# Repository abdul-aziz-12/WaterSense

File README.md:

# WaterSense
->A project of Water Motor Automation System
-> Contrains Arduino and Eagle PCB files for whole working project

Note: It also contains previous versions files.

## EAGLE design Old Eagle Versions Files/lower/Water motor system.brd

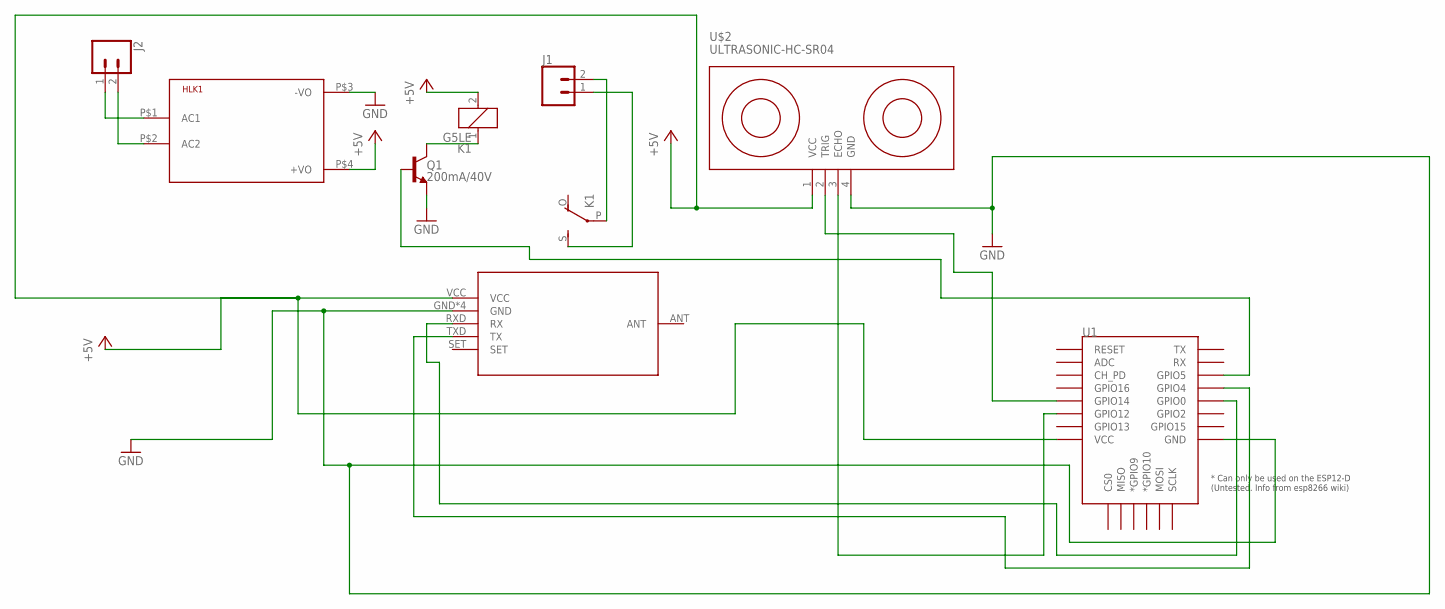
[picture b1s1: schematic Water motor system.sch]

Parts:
HLK1: HLK-PM013W; HLK-PM01
J1, J2: CONN_025MM; SCREWTERMINAL-5MM-2
K1: G5LE
Q1: 200mA/40V; TO-92
U1: ESP12ESMD; ESP12E-SMD
U$2: ULTRASONIC-HC-SR04
U$3: HC-12_FOOTPRINT

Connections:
+5V: HLK1.P$4 (+VO), K1.2, U1.VCC, U$2.1 (VCC), U$3.VCC
GND: HLK1.P$3 (-VO), Q1.1 (E), U1.GND, U$2.4 (GND), U$3.GND, U$3.GND1 (GND), U$3.GND2 (GND), U$3.MCHFIX (GND)
unnamed: U1.GPIO4, U$3.TXD (TX)
unnamed: U1.GPIO12, U$2.3 (ECHO)
unnamed: Q1.2 (B), U1.GPIO5
unnamed: J1.1, K1.S
unnamed: J1.2, K1.P
unnamed: K1.1, Q1.3 (C)
unnamed: HLK1.P$2 (AC2), J2.2
unnamed: HLK1.P$1 (AC1), J2.1
unnamed: U1.GPIO0, U$3.RXD (RX)
unnamed: U1.GPIO14, U$2.2 (TRIG)

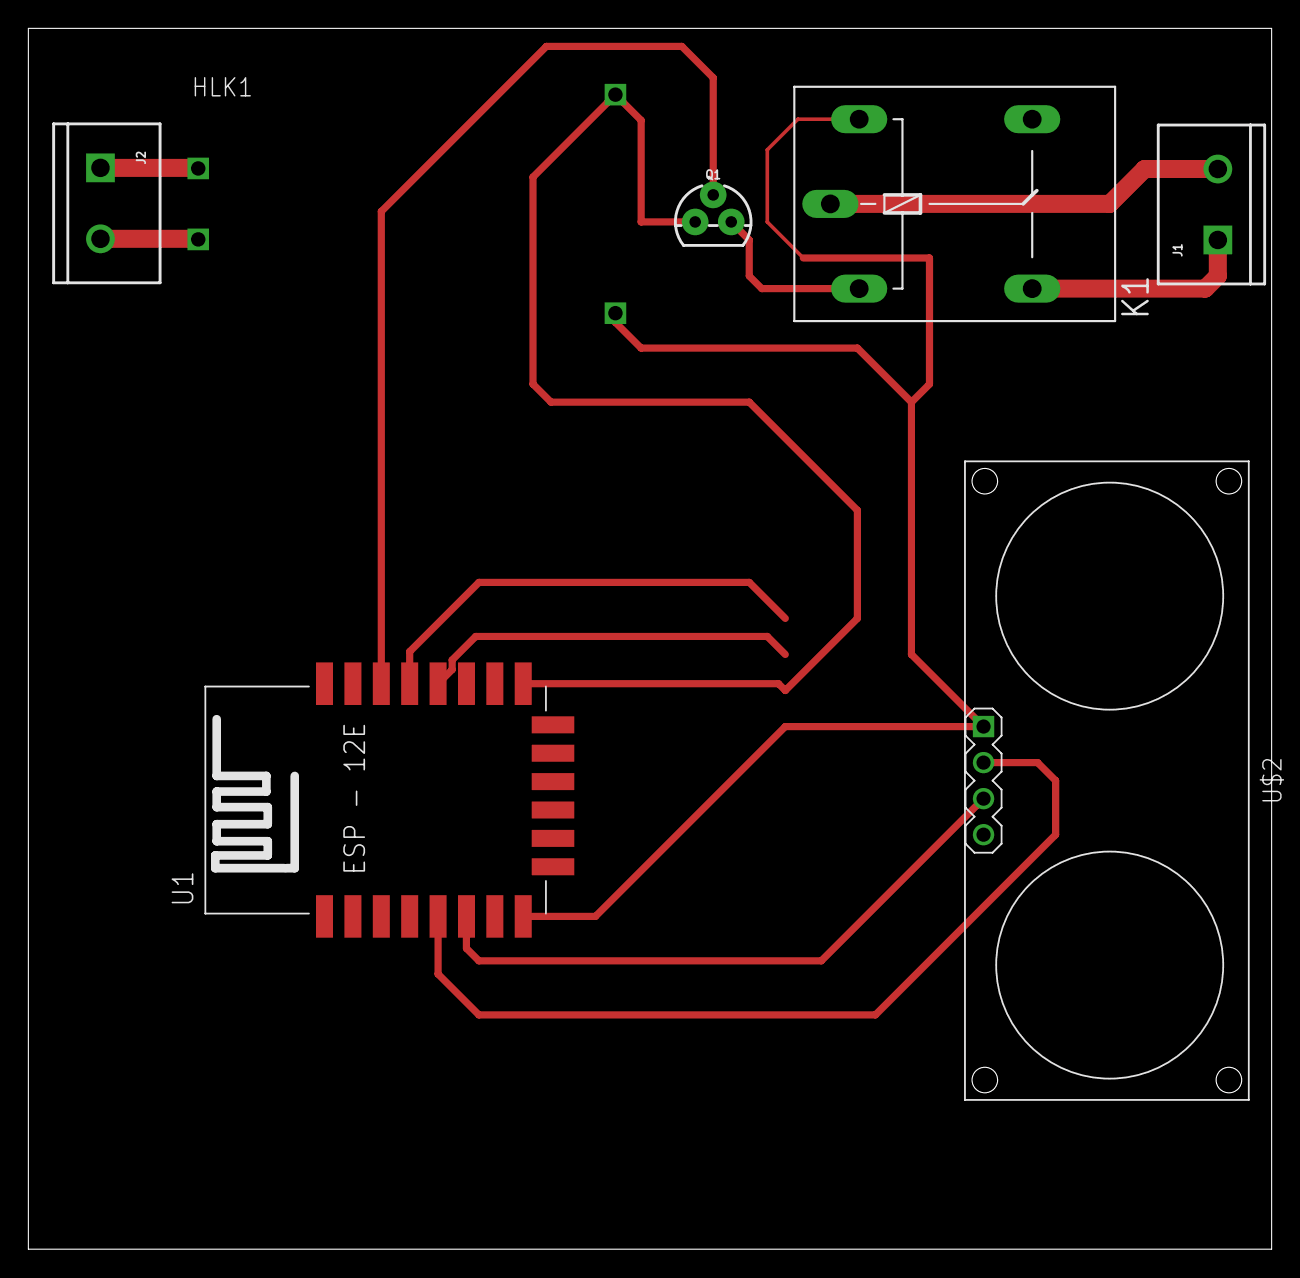
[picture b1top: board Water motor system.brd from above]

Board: 2 copper layers, 87.6 x 86.0 mm, 8 parts (1 on the bottom side), 12 nets.

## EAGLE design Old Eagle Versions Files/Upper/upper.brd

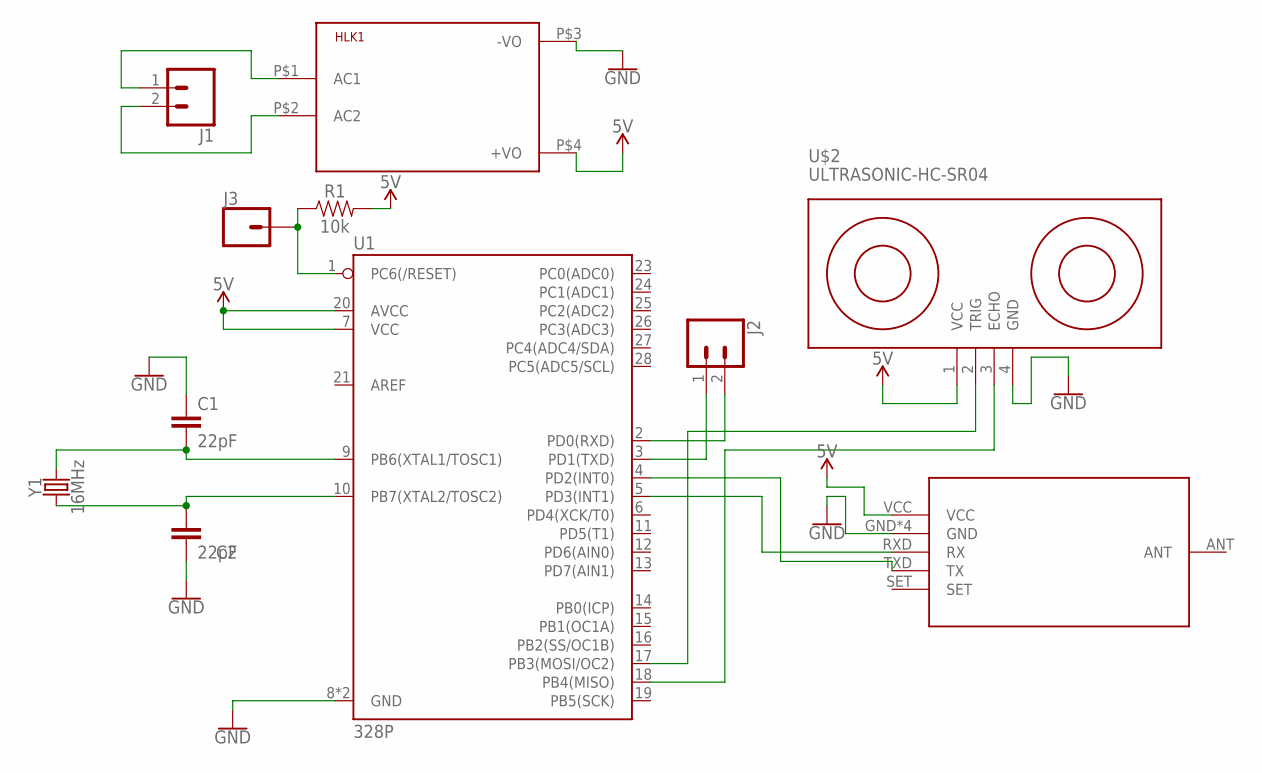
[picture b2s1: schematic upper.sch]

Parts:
C1, C2: 22pF; CAP-PTH-2.54
HLK1: HLK-PM013W; HLK-PM01
J1, J2: CONN_025MM; SCREWTERMINAL-5MM-2
J3: CONN_01; 1X01
R1: 10k; AXIAL-0.3
U1: 328P; DIP28
U$1: HC-12_FOOTPRINT
U$2: ULTRASONIC-HC-SR04
Y1: 16MHz; HC49US

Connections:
5V: HLK1.P$4 (+VO), R1.P$2 (2), U1.7 (VCC), U1.20 (AVCC), U$1.VCC, U$2.1 (VCC)
GND: C1.1, C2.2, HLK1.P$3 (-VO), U1.8 (GND), U1.22 (GND), U$1.GND, U$1.GND1 (GND), U$1.GND2 (GND), U$1.MCHFIX (GND), U$2.4 (GND)
unnamed: U1.4 (PD2(INT0)), U$1.TXD (TX)
unnamed: U1.17 (PB3(MOSI/OC2)), U$2.2 (TRIG)
unnamed: U1.18 (PB4(MISO)), U$2.3 (ECHO)
unnamed: U1.5 (PD3(INT1)), U$1.RXD (RX)
unnamed: HLK1.P$2 (AC2), J1.2
unnamed: HLK1.P$1 (AC1), J1.1
unnamed: J3.1, R1.P$1 (1), U1.1 (PC6(/RESET))
unnamed: J2.1, U1.3 (PD1(TXD))
unnamed: J2.2, U1.2 (PD0(RXD))
unnamed: C1.2, U1.9 (PB6(XTAL1/TOSC1)), Y1.2
unnamed: C2.1, U1.10 (PB7(XTAL2/TOSC2)), Y1.1

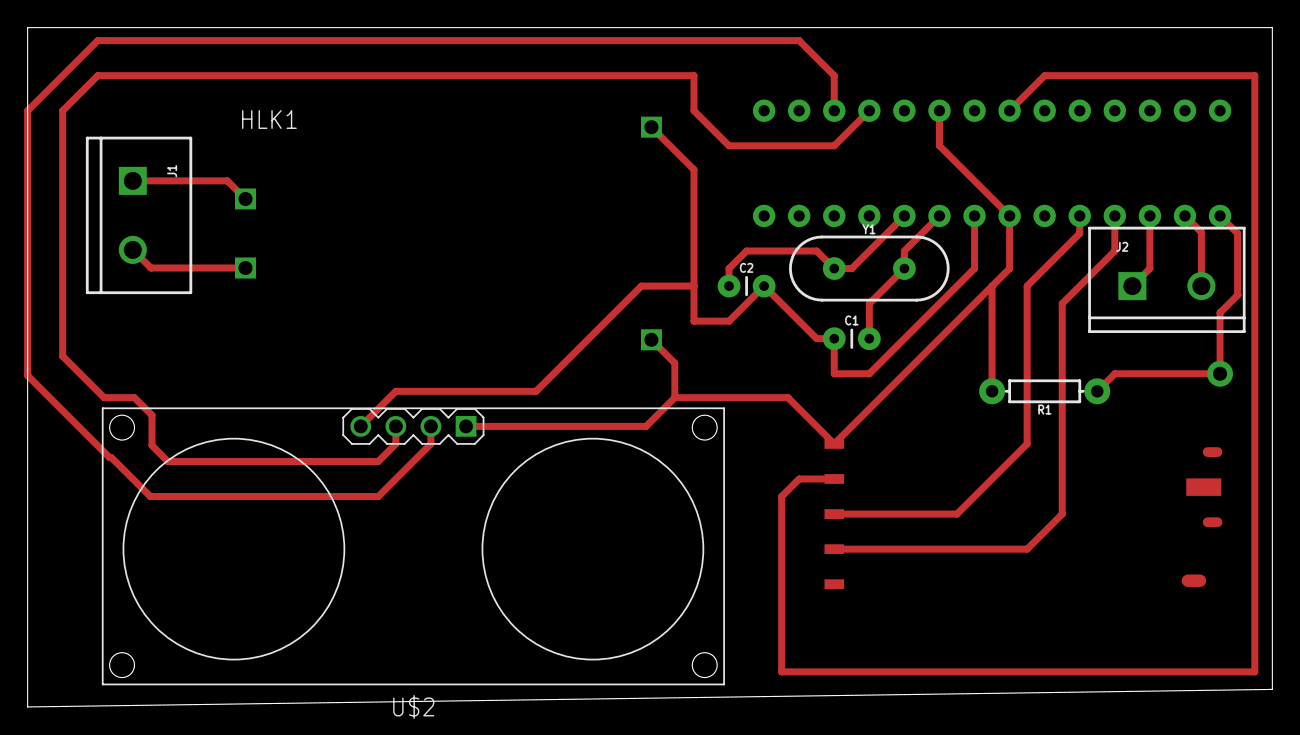
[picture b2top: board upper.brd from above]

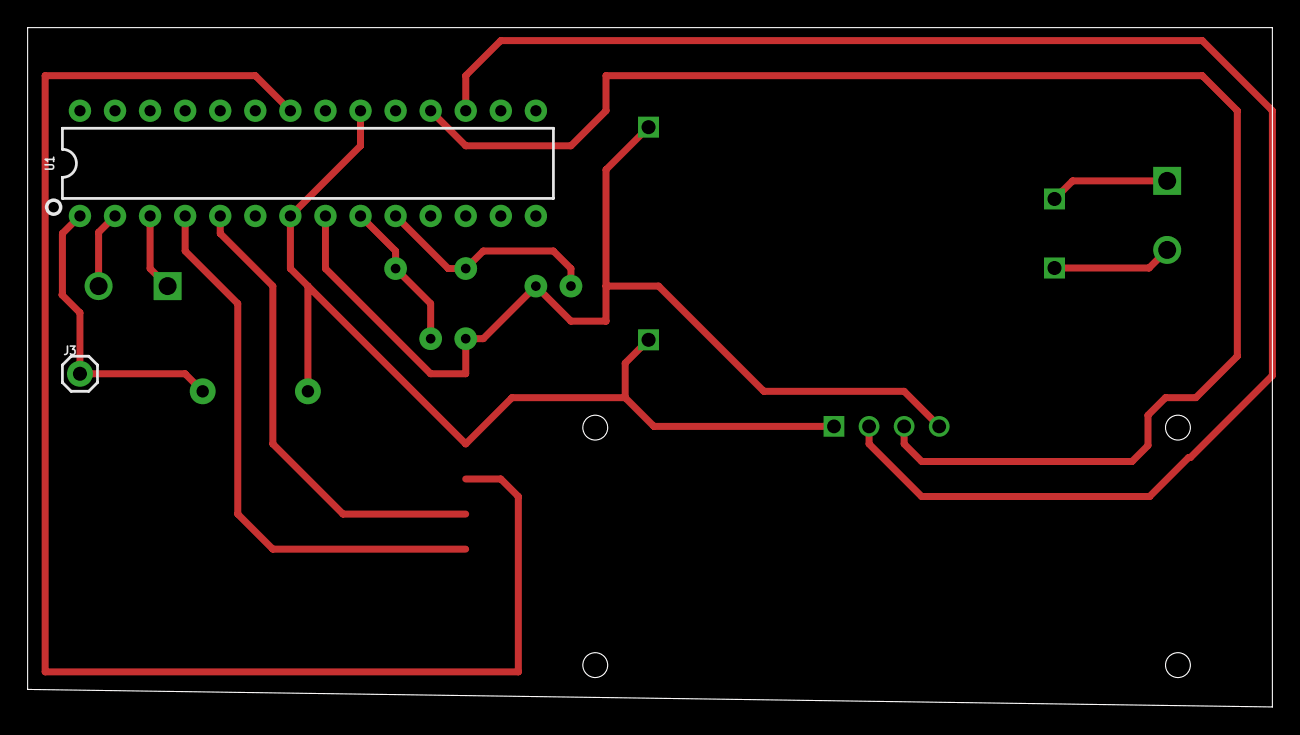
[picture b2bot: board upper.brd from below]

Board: 2 copper layers, 90.2 x 49.2 mm, 11 parts (2 on the bottom side), 13 nets.

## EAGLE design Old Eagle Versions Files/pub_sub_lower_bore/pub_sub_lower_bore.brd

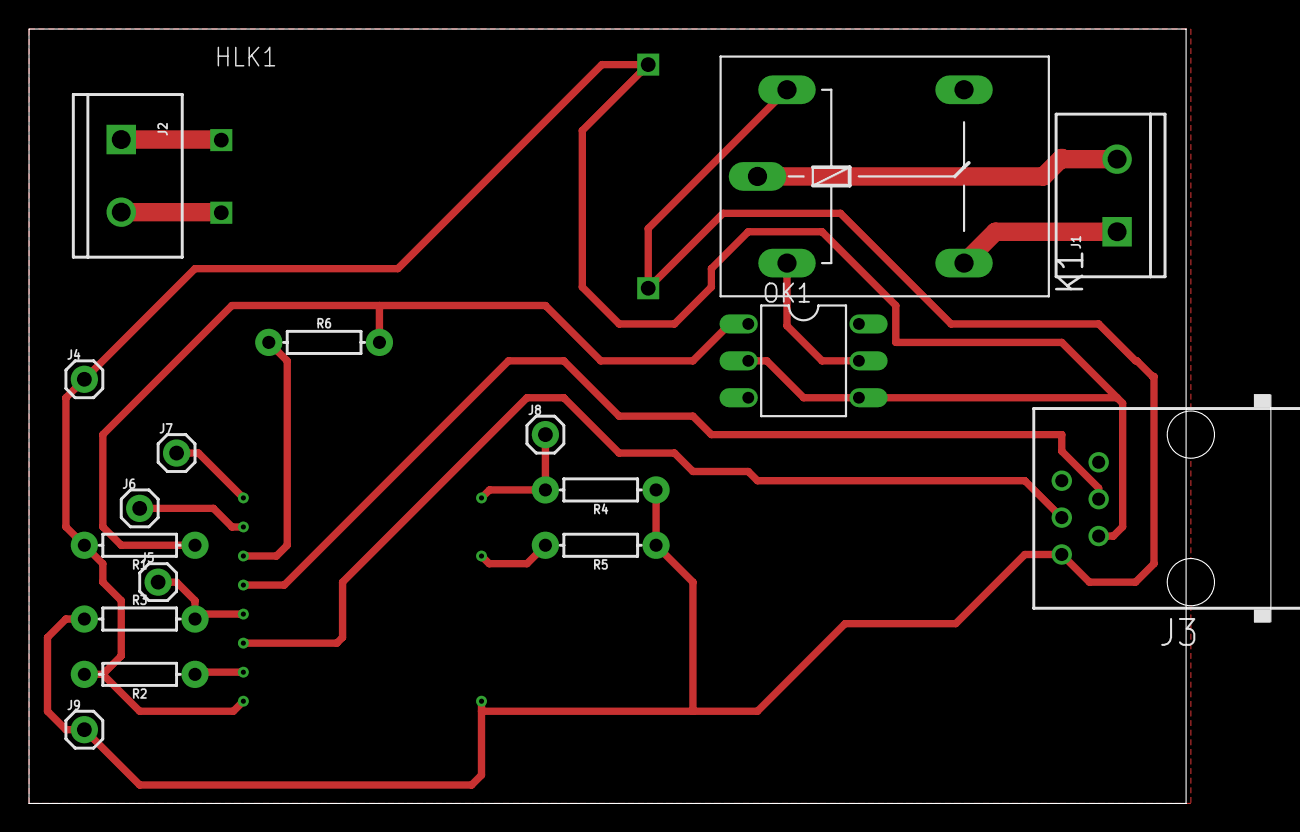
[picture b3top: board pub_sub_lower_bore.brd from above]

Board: 2 copper layers, 85.5 x 53.3 mm, 19 parts (1 on the bottom side), 17 nets.

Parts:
HLK1: HLK-PM013W; HLK-PM01
J1, J2: SCREWTERMINAL-5MM-2
J3: RJ11-6L-B; RJ11-NO_SHIELD
J4, J5, J6, J7, J8, J9: 1X01
K1: G5LE
OK1: 4N35; DIL06
R1: 10k; AXIAL-0.3
R2, R3, R4, R5, R6: 1k; AXIAL-0.3
U1: ESP12E-SMD

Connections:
+5V: HLK1.P$4, J3.1, J9.1, K1.2, R3.P$1, R4.P$1, R5.P$1, U1.VCC
GND: HLK1.P$3, J3.2, J4.1, OK1.2, OK1.4, R1.P$2, R2.P$2, U1.GND
unnamed: J3.4, U1.GPIO4
unnamed: OK1.1, R1.P$1, R6.P$2
unnamed: R2.P$1, U1.GPIO15
unnamed: J5.1, R3.P$2, U1.GPIO0
unnamed: R6.P$1, U1.GPIO5
unnamed: J1.1, K1.S
unnamed: J1.2, K1.P
unnamed: K1.1, OK1.5
unnamed: HLK1.P$2, J2.2
unnamed: HLK1.P$1, J2.1
unnamed: J3.3, U1.GPIO2
unnamed: J7.1, U1.TXD0
unnamed: J6.1, U1.RXD0
unnamed: J8.1, R4.P$2, U1.RESET
unnamed: R5.P$2, U1.CH_PD

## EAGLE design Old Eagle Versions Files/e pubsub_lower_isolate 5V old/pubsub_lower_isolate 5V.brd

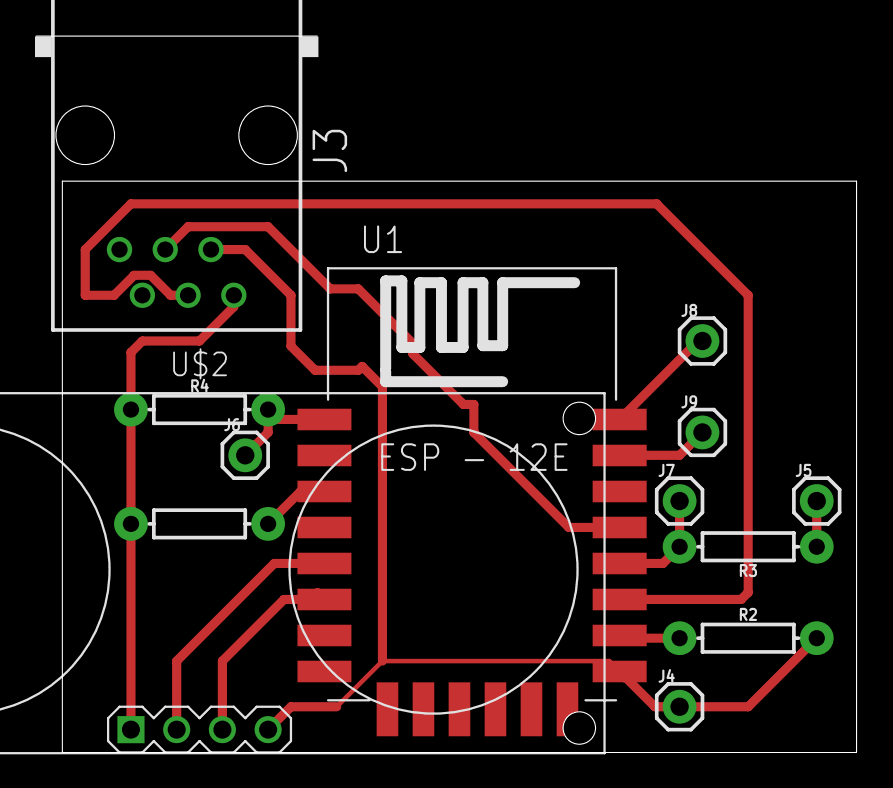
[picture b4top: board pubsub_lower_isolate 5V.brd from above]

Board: 2 copper layers, 44.1 x 31.7 mm, 13 parts (0 on the bottom side), 12 nets.

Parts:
J3: RJ11-6L-B; RJ11-NO_SHIELD
J4, J5, J6, J7, J8, J9: 1X01
R2, R3, R4, R5: 1k; AXIAL-0.3
U1: ESP12E-SMD
U$2: ULTRASONIC-HC-SR04

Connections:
+5V: J3.1, J5.1, R3.P$1, R4.P$1, R5.P$1, U1.VCC, U$2.1
GND: J3.2, J4.1, R2.P$2, U1.GND, U$2.4
unnamed: J3.4, U1.GPIO4
unnamed: R2.P$1, U1.GPIO15
unnamed: J7.1, R3.P$2, U1.GPIO0
unnamed: J9.1, U1.RXD0
unnamed: U1.GPIO12, U$2.3
unnamed: J3.3, U1.GPIO2
unnamed: U1.GPIO14, U$2.2
unnamed: J8.1, U1.TXD0
unnamed: J6.1, R4.P$2, U1.RESET
unnamed: R5.P$2, U1.CH_PD

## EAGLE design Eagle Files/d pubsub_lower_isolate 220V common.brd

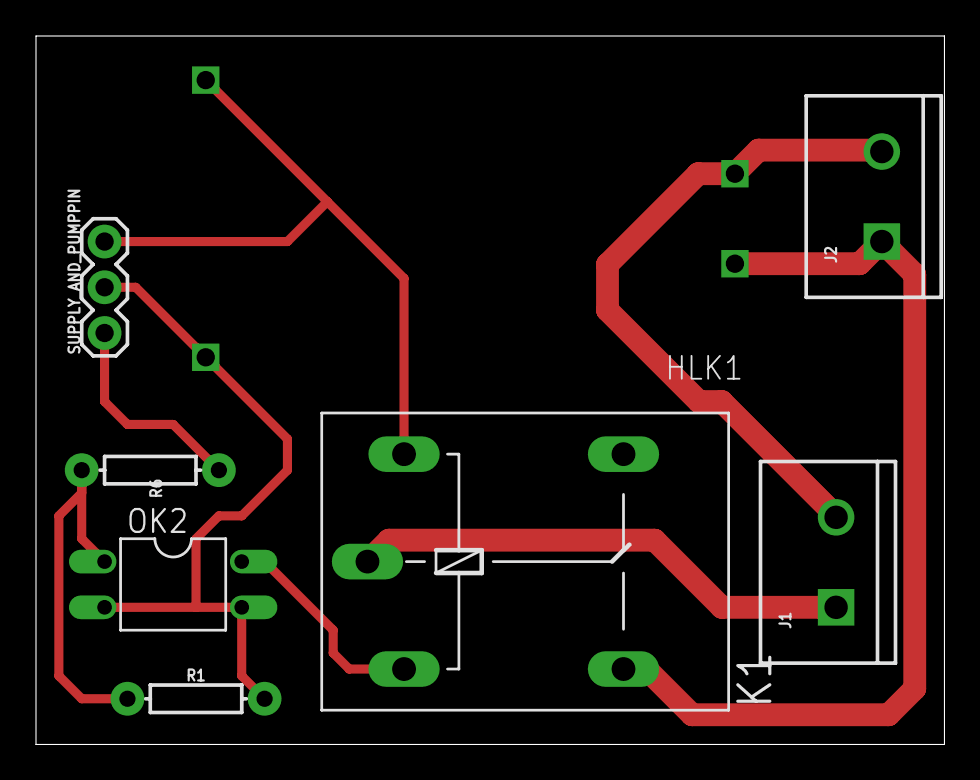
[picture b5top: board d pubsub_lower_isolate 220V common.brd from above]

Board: 2 copper layers, 50.5 x 39.4 mm, 8 parts (0 on the bottom side), 8 nets.

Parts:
HLK1: HLK-PM013W; HLK-PM01
J1, J2: SCREWTERMINAL-5MM-2
K1: G5LE
OK2: PC817; DIL04
R1: 10k; AXIAL-0.3
R6: 1k; AXIAL-0.3
SUPPLY_AND_PUMPPIN: 455-1750-1-ND; 1X03

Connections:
+5V: HLK1.P$4, K1.2, SUPPLY_AND_PUMPPIN.3
GND: HLK1.P$3, OK2.2, OK2.3, R1.P$2, SUPPLY_AND_PUMPPIN.2
unnamed: OK2.1, R1.P$1, R6.P$2
unnamed: HLK1.P$1, J2.1, K1.S
unnamed: J1.1, K1.P
unnamed: K1.1, OK2.4
unnamed: HLK1.P$2, J1.2, J2.2
PUMP_PIN: R6.P$1, SUPPLY_AND_PUMPPIN.1

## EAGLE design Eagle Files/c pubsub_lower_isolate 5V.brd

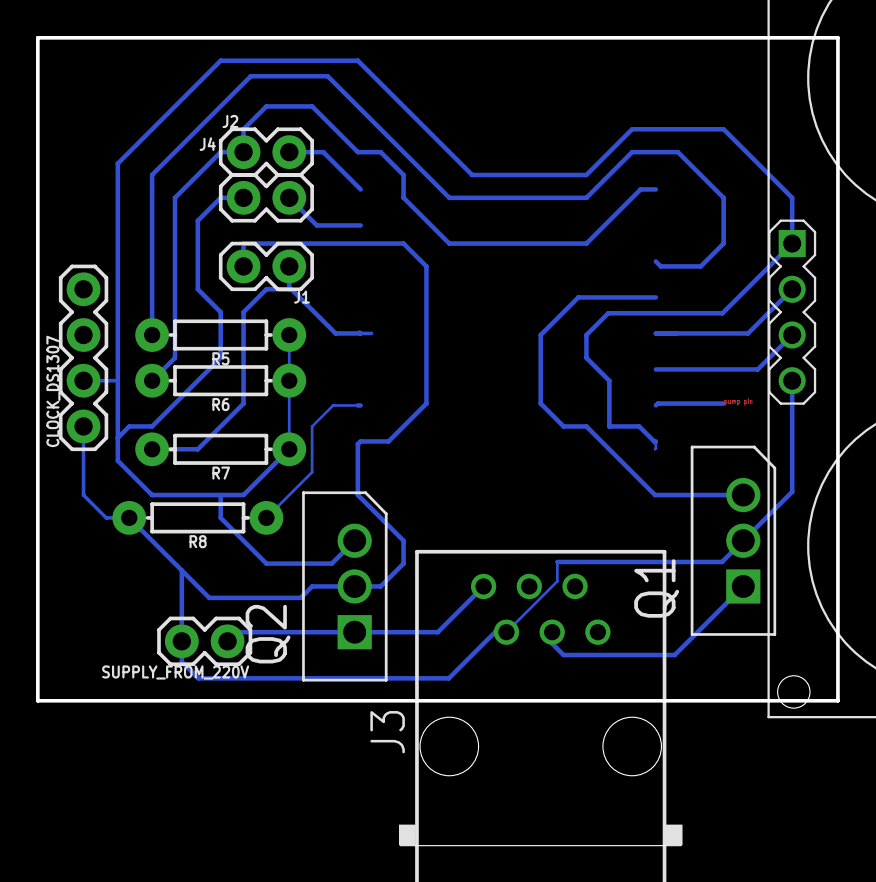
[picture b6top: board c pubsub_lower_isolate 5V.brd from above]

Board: 2 copper layers, 44.5 x 36.8 mm, 14 parts (1 on the bottom side), 15 nets.

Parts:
CLOCK_DS1307: 1X04
J1, J2, J4: 1X02
J3: RJ11-6L-B; RJ11-NO_SHIELD
Q1, Q2: LF33CV; TO254P450X1020X1935-3P
R5, R6, R7, R8: 10k; AXIAL-0.3
SUPPLY_FROM_220V: 1X02
U1: ESP12E-SMD
U$2: ULTRASONIC-HC-SR04

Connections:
5V: J3.1, Q2.1, SUPPLY_FROM_220V.1
GND: CLOCK_DS1307.1, J1.2, J3.2, Q1.2, Q2.2, R8.P$2, SUPPLY_FROM_220V.2, U1.GND, U$2.4
unnamed: R8.P$1, U1.GPIO15
unnamed: J2.2, U1.TXD0
unnamed: J2.1, R6.P$2, U1.RESET
unnamed: R5.P$2, U1.CH_PD
unnamed: J4.2, U1.RXD0
unnamed: CLOCK_DS1307.2, J4.1, Q2.3, R5.P$1, R6.P$1, R7.P$1, U1.VCC, U$2.1
unnamed: Q1.3, U1.GPIO16
unnamed: J3.4, Q1.1
unnamed: J1.1, R7.P$2, U1.GPIO0
unnamed: U1.GPIO14, U$2.2
unnamed: U1.GPIO12, U$2.3
SCL: CLOCK_DS1307.4, U1.GPIO5
SDA: CLOCK_DS1307.3, U1.GPIO4

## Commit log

2020-09-18 Eagle Files
2020-09-18 .brd file
2020-09-18 .sch file
2020-09-18 Create a pub_sub_upper system
2020-09-18 Create a_practical_receiver
2020-09-18 Rename a_practical_receiver to a_practical_receiver.ino
2020-09-18 Create Library
2020-09-18 Create Libraries
2020-12-29 Create Old Arduino Files versions

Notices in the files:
parts and their libraries:
diy-modules: Released under the Creative Commons Attribution 4.0 International License: http://creativecommons.org/licenses/by/4.0
SparkFun-Resistors: Licensing: Creative Commons ShareAlike 4.0 International - https://creativecommons.org/licenses/by-sa/4.0
